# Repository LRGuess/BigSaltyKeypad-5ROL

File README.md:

# Big-Salty-Keypad-5ROL
A 5 key Macropad with a rotary encoder, OLED display and 5 LEDs all using QMK firmware.

## Features
- Fully 3D Printable case
- 5 Programmable keys
- OLED display
- Rotary Encoder for volume control
- 5 LEDs for fun!

## CAD
This keypad comes together by sandwiching the PCB between the bottom and top parts of the case and fastening it together with 4 M3 screws. The 2 case peices are 3d printed as well as the rotary encoder's cap! I designed it in Fusion 360.

### Case parts and assembly:
Case:  
  
Assembly:  

## PCB
My PCB was designed in KiCAD, feel free to take a look at the designes below!  

### Schematic:  

### PCB:  

## Firmware
This keypad uses QMK firmware for everything!
- Encoder helps with volume control
- Programmable Keys using VIA
- OLED and LEDs!

## BOM
- 5x Cherry MX Switches
- 5x DSA Keycaps
- 4x M3x16mm SHCS Bolts
- 5x WS2812B LEDs
- 1x 0.91" 128x32 OLED Display
- 1x EC11 Rotary Encoder
- 1x XIAO RP2040
- 1x Case (2 printed parts)

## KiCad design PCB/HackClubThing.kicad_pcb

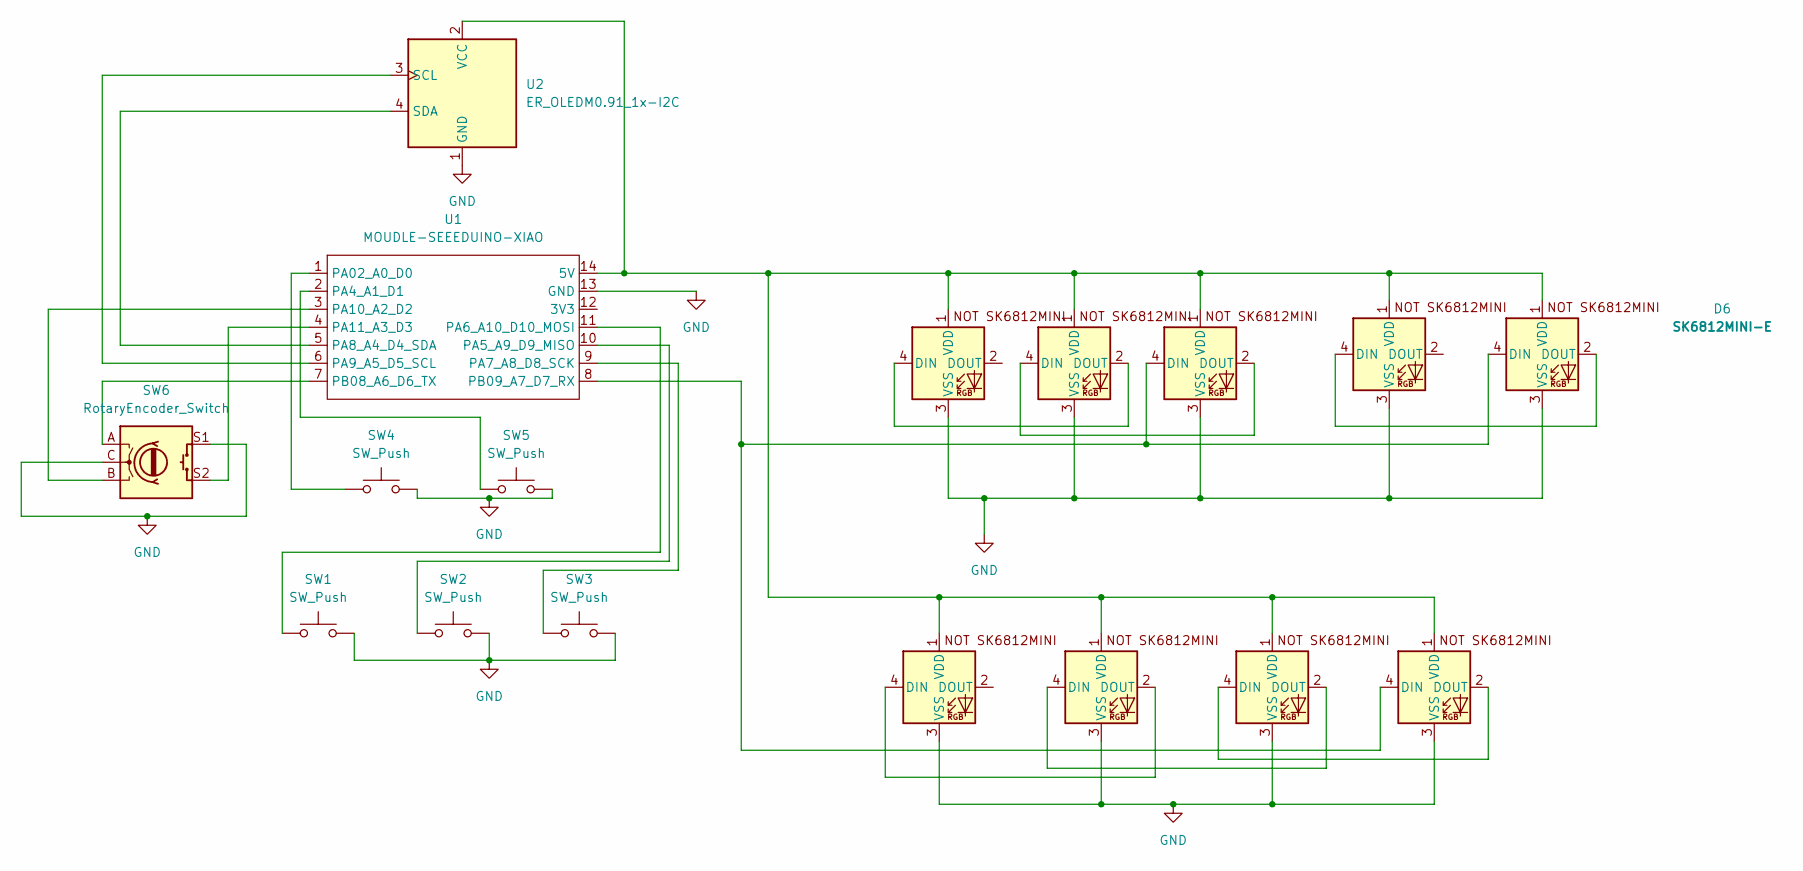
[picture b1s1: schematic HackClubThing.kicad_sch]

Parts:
D1, D2, D3, D4, D5, D6, D7, D8, D9: SK6812MINI-E; SK6812MINI-E_fixed
SW1, SW2, SW3, SW4, SW5: SW_Push; SW_Cherry_MX_1.00u_PCB
SW6: RotaryEncoder_Switch; RotaryEncoder_Alps_EC11E-Switch_Vertical_H20mm
U1: MOUDLE-SEEEDUINO-XIAO; XIAO-Generic-Hybrid-14P-2.54-21X17.8MM
U2: ER_OLEDM0.91_1x-I2C; SSD1306-0.91-OLED-4pin-128x32

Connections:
GND: D1.3 (VSS), D2.3 (VSS), D3.3 (VSS), D4.3 (VSS), D5.3 (VSS), D6.3 (VSS), D7.3 (VSS), D8.3 (VSS), D9.3 (VSS), SW1.2, SW2.2, SW3.2, SW4.2, SW5.2, SW6.C, SW6.S1, U1.13 (GND), U2.1 (GND)
unnamed: D1.4 (DIN), D7.2 (DOUT)
unnamed: D1.1 (VDD), D2.1 (VDD), D3.1 (VDD), D4.1 (VDD), D5.1 (VDD), D6.1 (VDD), D7.1 (VDD), D8.1 (VDD), D9.1 (VDD), U1.14 (5V), U2.2 (VCC)
unnamed: D2.4 (DIN), D3.2 (DOUT)
unnamed: D3.4 (DIN), D4.2 (DOUT)
unnamed: D4.4 (DIN), D6.4 (DIN), D9.4 (DIN), U1.8 (PB09_A7_D7_RX)
unnamed: D5.4 (DIN), D6.2 (DOUT)
unnamed: D7.4 (DIN), D8.2 (DOUT)
unnamed: D8.4 (DIN), D9.2 (DOUT)
unnamed: SW4.1, U1.1 (PA02_A0_D0)
unnamed: SW5.1, U1.2 (PA4_A1_D1)
unnamed: SW2.1, U1.10 (PA5_A9_D9_MISO)
unnamed: SW1.1, U1.11 (PA6_A10_D10_MOSI)
unnamed: SW3.1, U1.9 (PA7_A8_D8_SCK)
unnamed: U1.5 (PA8_A4_D4_SDA), U2.4 (SDA)
unnamed: U1.6 (PA9_A5_D5_SCL), U2.3 (SCL)
unnamed: SW6.B, U1.3 (PA10_A2_D2)
unnamed: SW6.S2, U1.4 (PA11_A3_D3)
unnamed: SW6.A, U1.7 (PB08_A6_D6_TX)

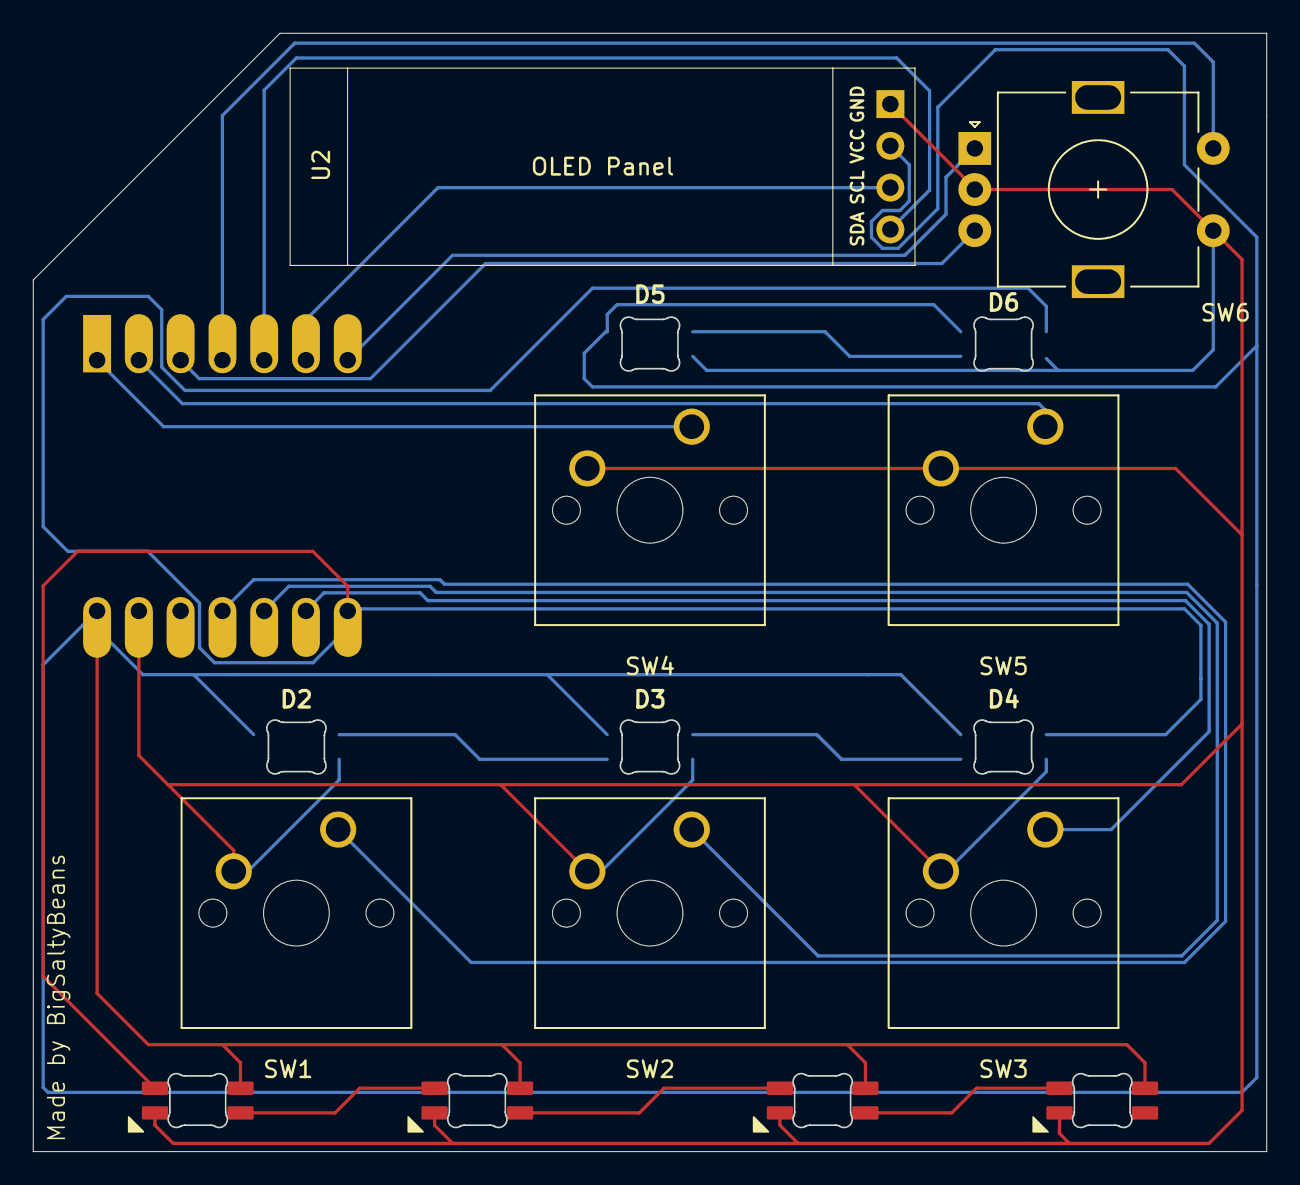
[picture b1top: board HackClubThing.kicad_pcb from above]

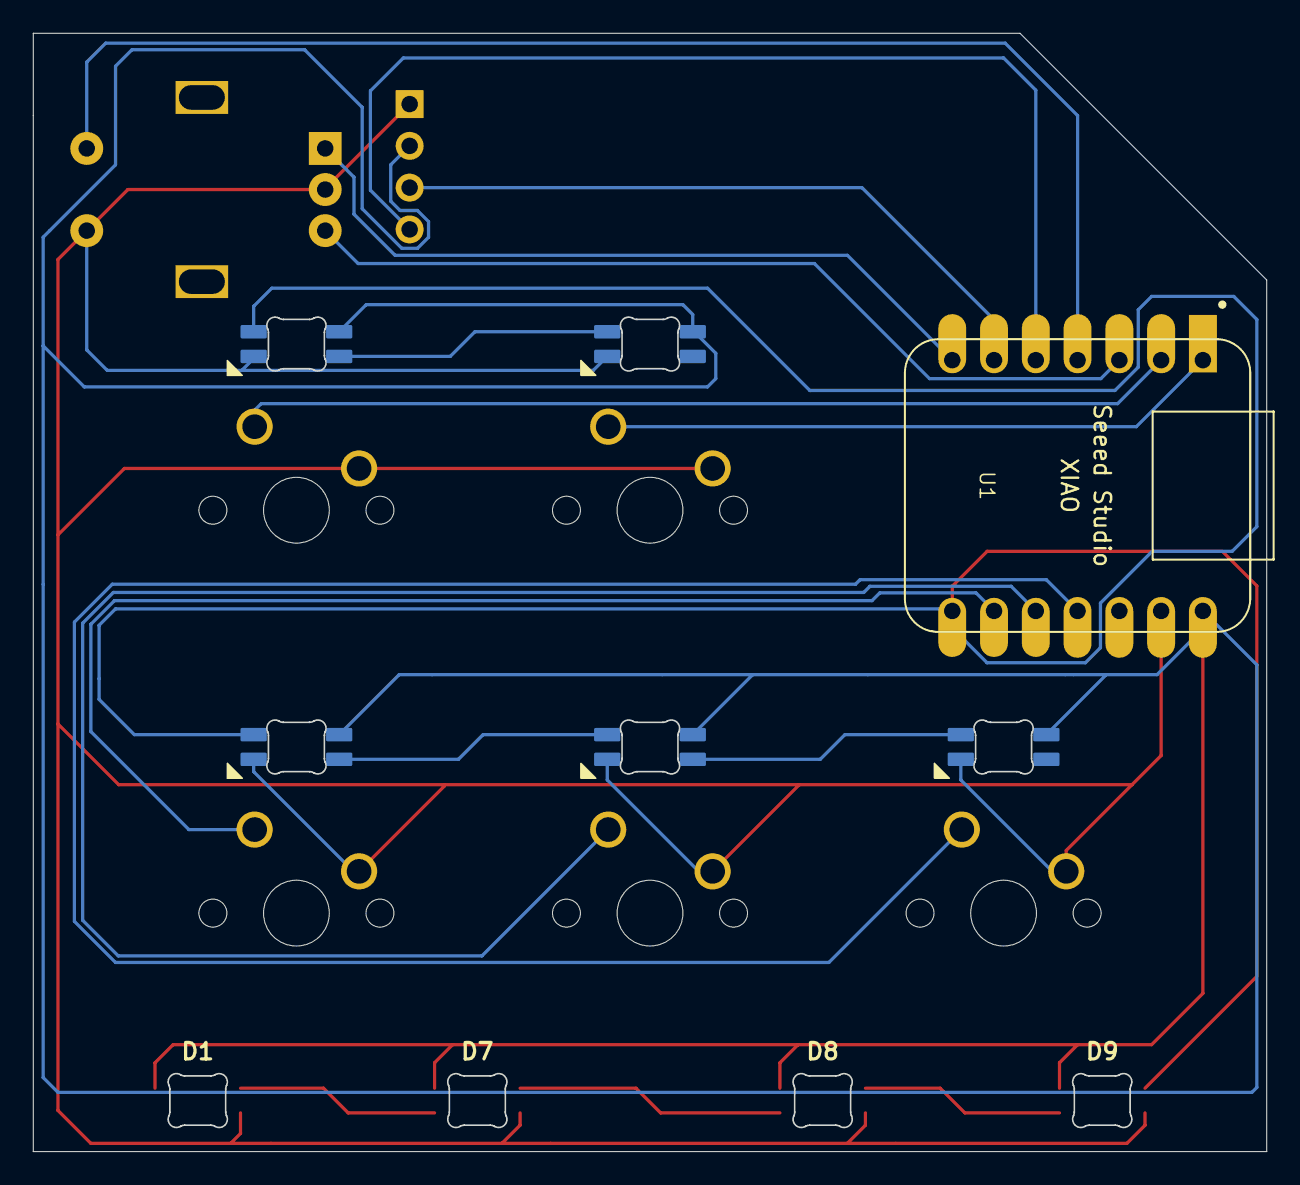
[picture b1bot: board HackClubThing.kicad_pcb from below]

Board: 2 copper layers, 75.0 x 68.0 mm, 17 parts (5 on the bottom side), 19 nets.

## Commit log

2026-06-11 BigSaltyKeypad 5ROL Source
2026-06-11 Revise README with detailed project information
    Updated the README to provide detailed features, CAD, PCB, firmware, and BOM information.
2026-06-11 Add case parts and assembly section to README
    Added sections for case parts and assembly with images.
2026-06-11 Added proper case CAD files
2026-06-11 Added entire CAD
2026-06-11 Created production folder and gerbers!
2026-06-11 Added firmware!
2026-06-11 Moved Key and LED Locations and added backlighting
